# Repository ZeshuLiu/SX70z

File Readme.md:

# SX-70z

## 介绍

### 项目组成
项目中包含几个部分的硬件：

1. [相机主控板](Hardware/MainController)：替换相机机头内原装的控制器，接管相机的控制。
2. [机身控制器](Hardware/Body_controller)：显示当前相机工作状态并提供用于交互的按键。粘贴在机身背部，不会增加相机高度，因此大部分相机包依旧可以通用，与相机主控板连接需要 Fpc 排线。

### 开发

PCB部分除FPC使用嘉立创EDA外均使用KiCad9绘制，仓库提供了相应的工程和光绘(gerber)文件。

机身控制器采用ESP-IDF进行开发

## 性能参数
相机主控可以单独使用，此时可以进行自动测光和曝光，如果需要使用B、T以及手动模式需要配备机身控制器。

**快门速度：** 3s-1/8000s，共 27 档，支持 B 门及 T 门 。 T 门可设置时间，至多5h （非定时T和B门无时间限制）\
**自拍定时：** 0s/2s/5s/10s （倒计时完成后按当前模式自动曝光，倒计时期间挂起其余 Core 1 任务，不受按键干扰）\
**多重曝光：** 最多 11 张（受 MCU 机能限制，曝光过程中无法折叠相机，断电将导致快门保持打开状态造成严重过曝）。多重曝光期间电磁铁持续通电，间隔超过 5 分钟可能导致过热，建议尽快完成所有曝光并吐片。设置方式：长按进入设置菜单，切换 MultiExp 选项（-1 为仅中止/首张防护，0 为正常拍摄，1-10 为额外曝光张数）\
**测光：** 支持 ISO 640 相纸（通过 OPT4001 环境光传感器 + 窗口衰减系数 `METERING_ATTEN_K` 标定），实测与 **Sekonic L-308S** 测光表对比，全快门速度范围（3s – 1/8000s）精度一致，自动测光下最低快门速度 3s  \
**闪光同步：** 插入闪光灯后快门速度自动锁定 1/30s，手动模式可设置慢于 1/30s 进行填充闪光

*SX70的光圈在使用闪光灯时将会根据对焦距离进行收缩，此时调整黑白轮可以控制其光圈大小。本项目依旧保留了该特点，因此在使用闪光灯时请注意对焦距离以及黑白轮的位置*

### 曝光模式 × 闪光灯 行为矩阵

| 模式 | 无闪光灯 | 有闪光灯 |
|------|---------|---------|
| **AUTO** | 测光 → 自动选快门速度 → 普通曝光 | 快门固定 1/30s → 闪光曝光（47ms 预延迟后触发电容引闪） |
| **BULB** | 开快门 → 等 S1T 释放 → 关快门 | SOL2 光圈打开 → 开快门 → 47ms → 闪光 → 等 S1T 释放 |
| **TIME** | 开快门 → 等 S1T 按两次 → 关快门 | SOL2 光圈打开 → 开快门 → 47ms → 闪光 → 等 S1T 按两次 |
| **MANUAL** | 用户指定快门速度 → 普通曝光 | 快门限制在 1/30s，按用户速度计算 gap → 闪光曝光 |

所有模式下，相机任务均运行在 **ESP32 的 Core 1**，按优先级分层隔离，曝光时序不受 WiFi/BLE 干扰。

### 软件架构

```
Core 0:   WiFi 协议栈 + NimBLE BLE + HTTP Server (OTA Web) + 事件回调
Core 1:   相机控制（与射频中断隔离）
  ├─ Shutter  Task  prio 10 — 强时序引脚控制（busy-wait，独占 Core 1）
  ├─ Control  Task  prio 8  — 主控逻辑（按键/模式/S1 快门）
  ├─ Display  Task  prio 5  — SSD1306 I2C 刷屏（200ms 周期）
  └─ Metering Task  prio 3  — OPT4001 测光（1s 周期）
```

模块文件：

| 文件 | 职责 |
|------|------|
| `camera_main.c` | 任务调度、曝光时序、电磁铁/电机控制 |
| `gpio_inputs.c` | GPIO 输入处理：S1/S2 去抖、3D 按键、设置菜单（自拍定时 / 多重曝光 / IP 显示） |
| `display_manager.c` | OLED 帧绘制、倒计时显示、设置菜单布局 |
| `opt4001.c` | OPT4001 环境光传感器 I2C 驱动 |
| `ssd1306.c` | SSD1306 OLED I2C 驱动（esp_lcd 后端，含 `ssd1306_draw_str_black` 反色绘制） |
| `pcf8575.c` | PCF8575 I2C GPIO 扩展驱动 |
| `pin_init.c` | GPIO 引脚初始化 |
| `ota_web.c` | WiFi HTTP OTA 网页升级 |

### 设置菜单

长按 3D 按键的"按下"键进入设置菜单，菜单参数化支持上下键切换选项、短按"按下"键切换调整/浏览模式：

| 选项 | 说明 |
|------|------|
| **SelfTimer** | 自拍定时：0s / 2s / 5s / 10s |
| **MultiExp** | 多重曝光：-1（仅中止，首张防护）/ 0（正常）/ 1-10（额外张数，最多 11 张）|
| **IP Addr** | 只读，显示相机当前 WiFi IP 地址（未连接时显示 "not connected"）|

状态栏右上角同时显示当前自拍定时值与多重曝光剩余张数。

## 样片

## 硬件制造
投产文件集中在 [投产文件](投产文件/)：主控使用 3.5 版 Gerber，机身控制器、机身 FPC 和外壳文件也在其中。BOM、坐标和硬件版本的对应关系仍须按目录说明核对后再下单。PCB 厚度应小于 0.8 mm，主板与机身控制器通过 FPC 连接。完整操作草稿见[复刻与调试指南](Code/SX70z_ESP/SX70_ModelZ/复刻指南.md)。

## 软件

在将机身主控安装至机器内部之前需要将固件通过串口烧录至控制器中。后续可以通过 OTA 无线升级，无需拆机。

**首次 WiFi 配网：**

首次开机相机没有 WiFi 凭据，会通过 BLE 广播 `SX70z_POP`。手机下载 **ESP BLE Provisioning** 应用（iOS/Android 应用商店均有），打开后选择配网，输入配对密钥 `sx70z123`，选择家中 WiFi 并输入密码即可。配网成功后凭据会存入 NVS，下次开机自动连接。

**OTA 升级方式：**
1. 相机开机连接 WiFi（通过 BLE 配网或已保存的凭据自动连接）
2. 手机或电脑连接同一局域网，浏览器打开相机 IP（OLED 设置菜单中可查看）
3. 选择编译好的 `.bin` 固件文件上传
4. 上传完成自动重启，新固件生效（Bootloader 会校验固件有效性，异常自动回滚）

快门可通过 `http://<相机IP>/calibration` 页面校准并保存，无需修改源码。先将 1/8000 调到快门形成一个小缝，其余档位可参考该档的偏移量在默认值基础上调整，再逐档测量确认；具体操作可搜索“陆工主板 快门校准”教程，也可使用[快门速度测试器](https://github.com/ZeshuLiu/ShutterSpeedCalibrator)。详细说明见[复刻与调试指南](Code/SX70z_ESP/SX70_ModelZ/复刻指南.md)。

## 组装
> 提示：组装需要一些基本的工具：电烙铁、撬棒和镊子。 \
大多数sx70相机的螺丝都是非常特殊的1mm x 1mm 宝丽来螺丝，拆卸需要特殊的螺丝刀，可以从咸鱼买一把或者自己磨一个。 \
在操作之前推荐先浏览以下内容[Disassembly Guide](https://instantphotography.files.wordpress.com/2010/12/polaroid-sx-70-camera-repair-book.pdf) 或者 [SX70 camera 125ASA to 600ASA conversion](https://opensx70.com/tutorials/100-600-conversion/).

拆卸后对原本主板进行替换即可，如需要机身控制器则将左上角焊盘焊线引出即可通过转接板连接机身控制器。焊接FPC时建议使用含铅(低温)焊锡，否则有损伤机器FPC的风险。只需要将原本的拆掉并且替换上去即可，对于有焊接及机身拆装经验的人来说难度不高。

### 相关开源软件

1. 项目受到了[OPSX ](https://github.com/sunyitong/OPSX)和[openSX70](https://github.com/openSX70)的启发。

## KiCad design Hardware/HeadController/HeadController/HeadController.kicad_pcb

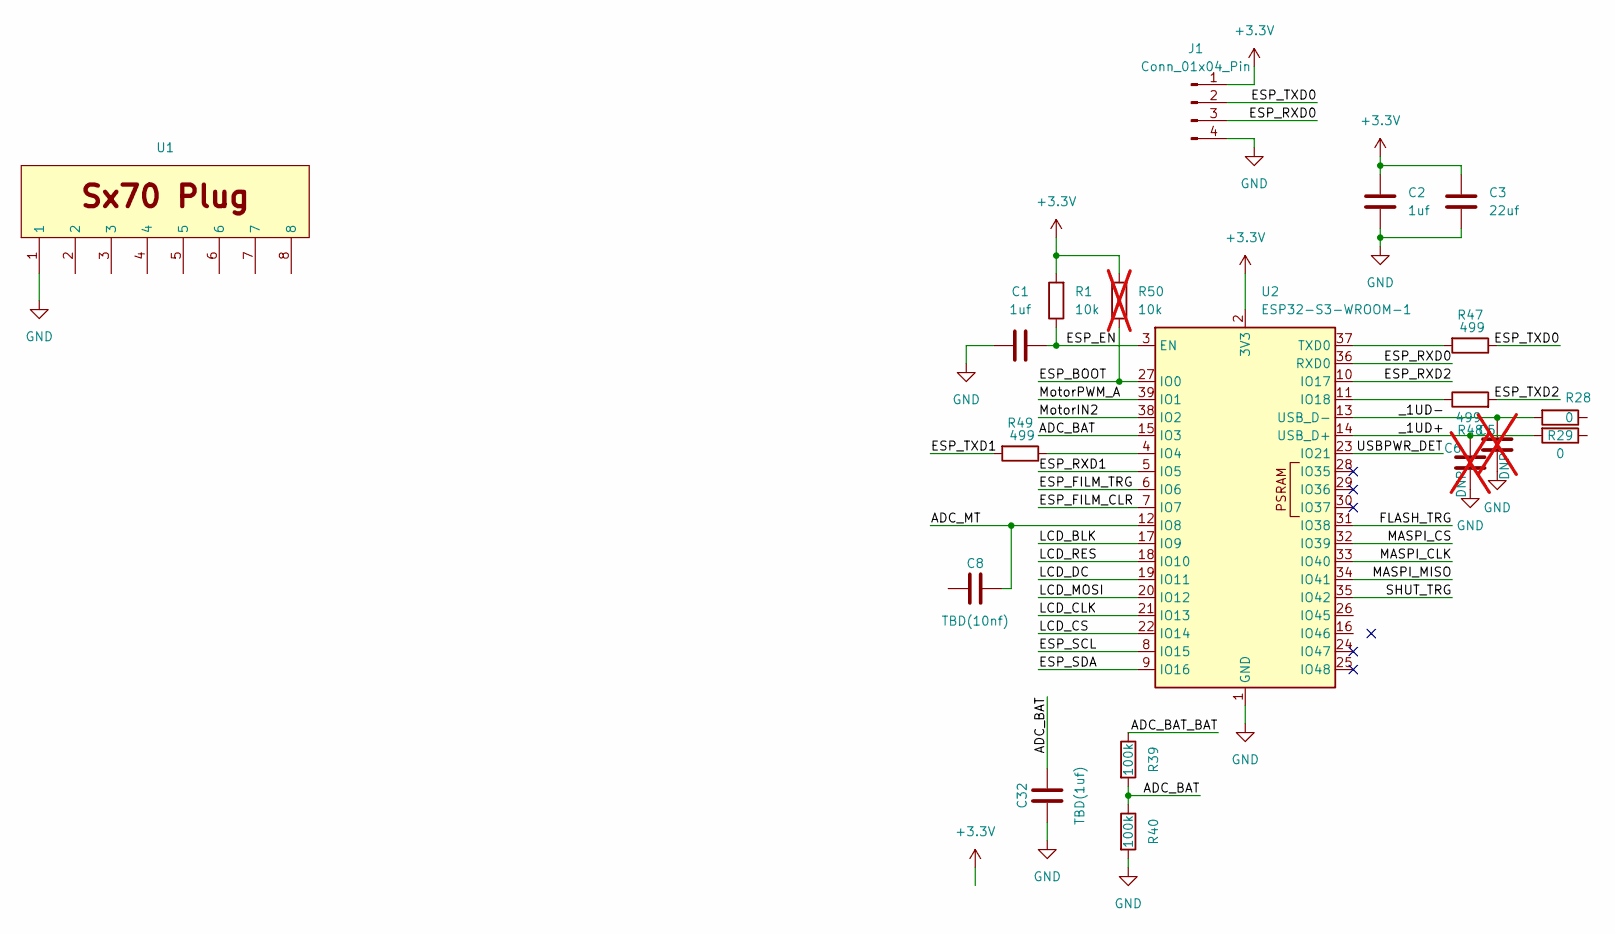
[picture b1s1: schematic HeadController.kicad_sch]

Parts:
C1, C2: 1uf; C_0603_1608Metric
C3: 22uf; C_0805_2012Metric
C5, C6: DNP; C_0603_1608Metric; not fitted
C8: TBD(10nf); C_0603_1608Metric
C32: TBD(1uf); C_0603_1608Metric
J1: Conn_01x04_Pin; PinHeader_1x04_P1.27mm_Vertical
R1: 10k; R_0603_1608Metric
R28, R29: 0; R_0603_1608Metric
R39, R40: 100k; R_0603_1608Metric
R47, R48, R49: 499; R_0603_1608Metric
R50: 10k; R_0603_1608Metric; not fitted
U1: SX70_Flash_Plug
U2: ESP32-S3-WROOM-1

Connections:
+3.3V: C2.2, C3.2, J1.1, R1.2, R50.2, U2.2 (3V3)
/ADC_BAT: C32.2, R39.2, R40.1, U2.15 (IO3)
/ADC_BAT_BAT: R39.1
/ADC_MT: C8.2, U2.12 (IO8)
/ESP_BOOT: R50.1, U2.27 (IO0)
/ESP_EN: C1.2, R1.1, U2.3 (EN)
/ESP_FILM_CLR: U2.7 (IO7)
/ESP_FILM_TRG: U2.6 (IO6)
/ESP_RXD0: J1.3, U2.36 (RXD0)
/ESP_RXD1: U2.5 (IO5)
/ESP_RXD2: U2.10 (IO17)
/ESP_SCL: U2.8 (IO15)
/ESP_SDA: U2.9 (IO16)
/ESP_TXD0: J1.2, R47.1
/ESP_TXD1: R49.2
/ESP_TXD2: R48.2
/FLASH_TRG: U2.31 (IO38)
/LCD_BLK: U2.17 (IO9)
/LCD_CLK: U2.21 (IO13)
/LCD_CS: U2.22 (IO14)
/LCD_DC: U2.19 (IO11)
/LCD_MOSI: U2.20 (IO12)
/LCD_RES: U2.18 (IO10)
/MASPI_CLK: U2.33 (IO40)
/MASPI_CS: U2.32 (IO39)
/MASPI_MISO: U2.34 (IO41)
/MotorIN2: U2.38 (IO2)
/MotorPWM_A: U2.39 (IO1)
/SHUT_TRG: U2.35 (IO42)
/USBPWR_DET: U2.23 (IO21)
/_1UD+: C6.2, R29.2, U2.14 (USB_D+)
/_1UD-: C5.2, R28.2, U2.13 (USB_D-)
GND: C1.1, C2.1, C3.1, C5.1, C6.1, C32.1, J1.4, R40.2, U1.1 (1_1), U2.1 (GND), U2.40 (GND), U2.41 (GND)
unnamed: R49.1, U2.4 (IO4)
unnamed: R48.1, U2.11 (IO18)
unnamed: R47.2, U2.37 (TXD0)

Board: 2 copper layers, 19 parts (0 on the bottom side), 13 nets, no tracks yet.

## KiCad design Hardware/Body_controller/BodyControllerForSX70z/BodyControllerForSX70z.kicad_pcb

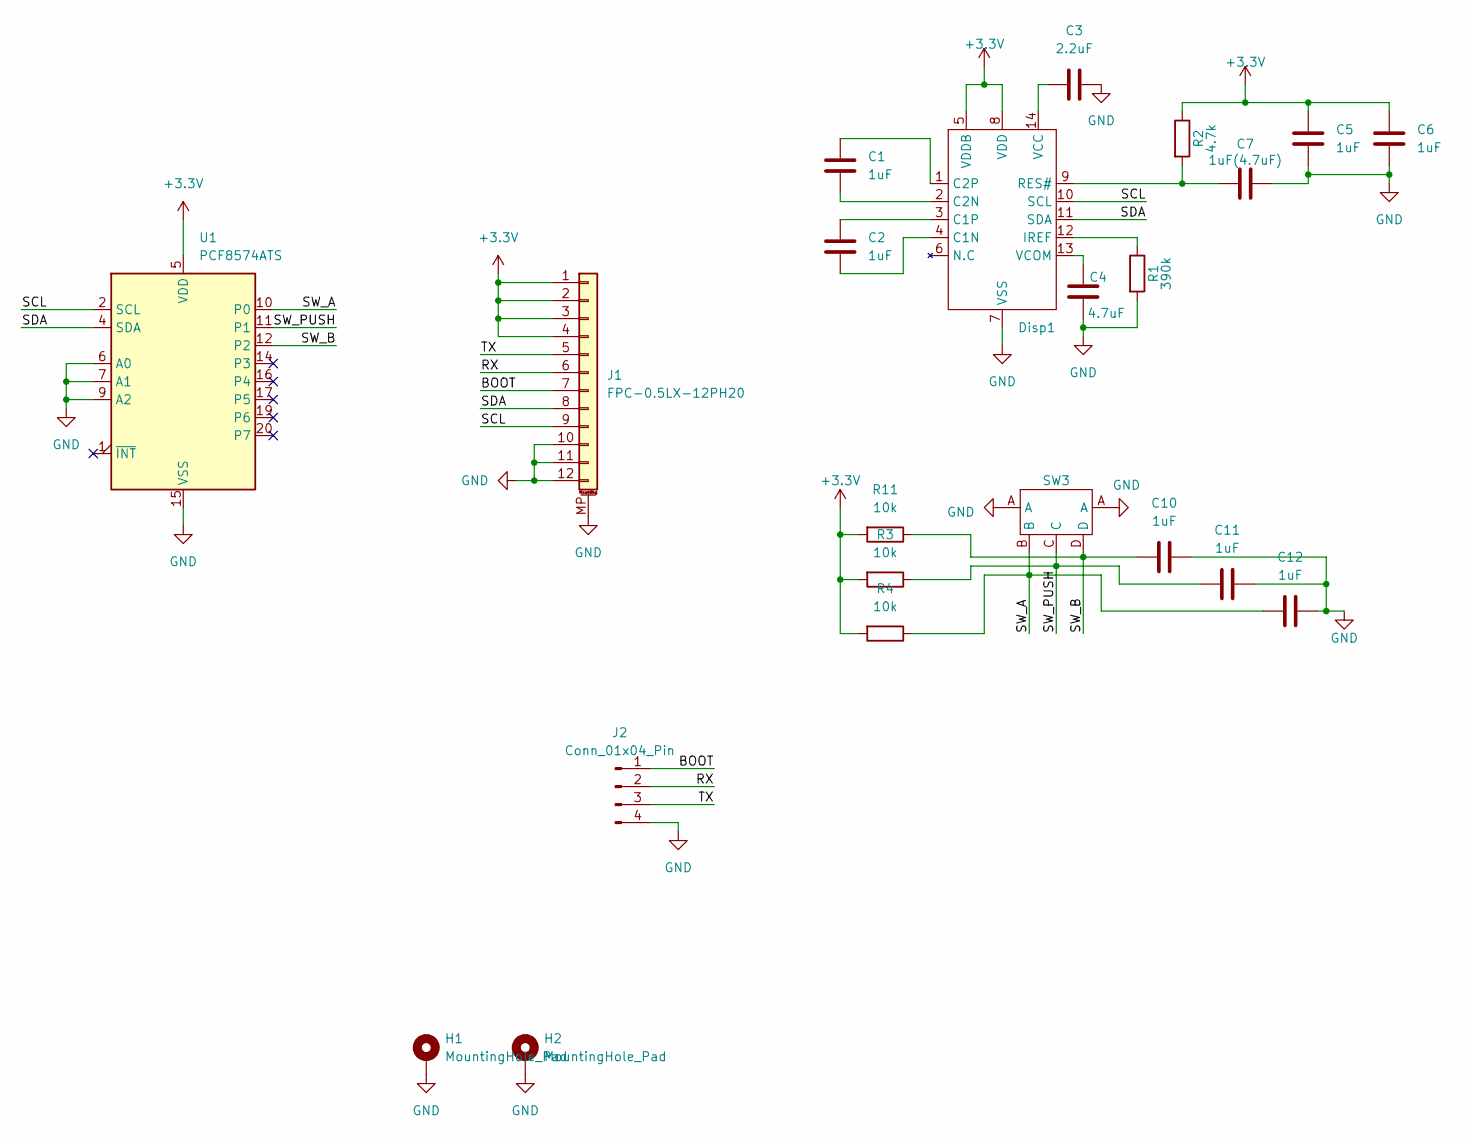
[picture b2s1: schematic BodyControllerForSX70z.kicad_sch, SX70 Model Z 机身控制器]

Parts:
C1, C2, C5, C6, C10, C11, C12: 1uF; C_0603_1608Metric_Pad1.08x0.95mm_HandSolder
C3: 2.2uF; C_0603_1608Metric_Pad1.08x0.95mm_HandSolder
C4: 4.7uF; C_0603_1608Metric_Pad1.08x0.95mm_HandSolder
C7: 1uF(4.7uF); C_0603_1608Metric_Pad1.08x0.95mm_HandSolder
Disp1: SSD1306_0.91_i2c
H1, H2: MountingHole_Pad; MountingHole_3.2mm_M3_DIN965_Pad
J1: FPC-0.5LX-12PH20
J2: Conn_01x04_Pin; PinHeader_1x04_P2.54mm_Horizontal
R1: 390k; R_0603_1608Metric_Pad0.98x0.95mm_HandSolder
R2: 4.7k; R_0603_1608Metric_Pad0.98x0.95mm_HandSolder
R3, R4, R11: 10k; R_0603_1608Metric_Pad0.98x0.95mm_HandSolder
SW3: Direction3 Pin5
U1: PCF8574ATS; SSOP-20_4.4x6.5mm_P0.65mm

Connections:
+3.3V: C5.1, C6.1, Disp1.5 (VDDB), Disp1.8 (VDD), J1.1, J1.2, J1.3, J1.4, R2.1, R3.2, R4.2, R11.2, U1.5 (VDD)
/BOOT: J1.7, J2.1
/RX: J1.6, J2.2
/SCL: Disp1.10 (SCL), J1.9, U1.2 (SCL)
/SDA: Disp1.11 (SDA), J1.8, U1.4 (SDA)
/SW_A: C12.1, R4.1, SW3.B, U1.10 (P0)
/SW_B: C10.1, R11.1, SW3.D, U1.12 (P2)
/SW_PUSH: C11.1, R3.1, SW3.C, U1.11 (P1)
/TX: J1.5, J2.3
GND: C3.2, C4.1, C5.2, C6.2, C7.2, C10.2, C11.2, C12.2, Disp1.7 (VSS), H1.1, H2.1, J1.10, J1.11, J1.12, J1.MP (MountPin), J2.4, R1.2, SW3.A, U1.6 (A0), U1.7 (A1), U1.9 (A2), U1.15 (VSS)
unnamed: C2.2, Disp1.4 (C1N)
unnamed: C2.1, Disp1.3 (C1P)
unnamed: C1.2, Disp1.2 (C2N)
unnamed: C1.1, Disp1.1 (C2P)
unnamed: Disp1.12 (IREF), R1.1
unnamed: C7.1, Disp1.9 (RES#), R2.2
unnamed: C3.1, Disp1.14 (VCC)
unnamed: C4.2, Disp1.13 (VCOM)

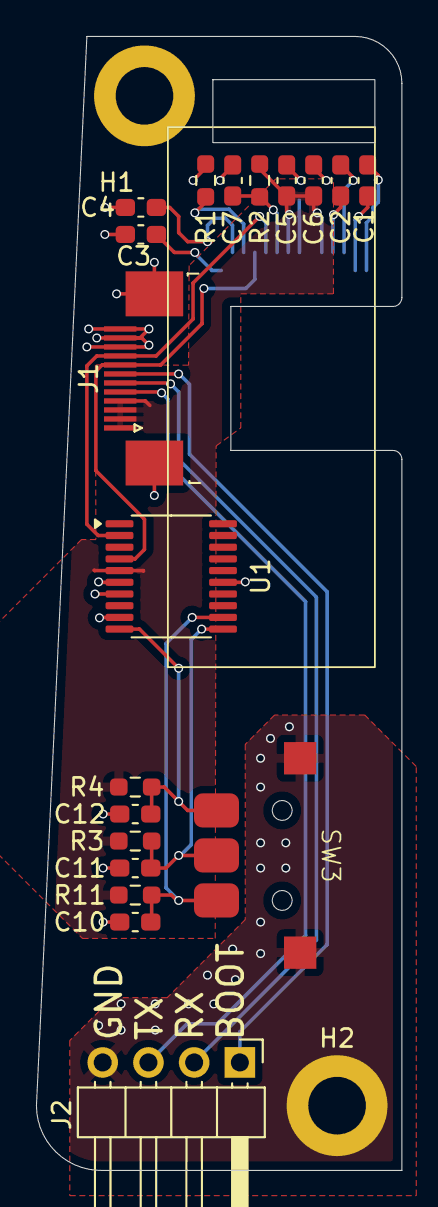
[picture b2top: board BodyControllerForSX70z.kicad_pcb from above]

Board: 2 copper layers, 20.3 x 63.0 mm, 22 parts (1 on the bottom side), 18 nets.

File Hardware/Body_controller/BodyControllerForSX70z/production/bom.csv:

Designator,Footprint,Quantity,Value,LCSC Part #
"C1, C10, C11, C12, C2, C5, C6",0603,7,1uF,
C3,0603,1,2.2uF,
C4,0603,1,4.7uF,
C7,0603,1,1uF(4.7uF),
DISP1,SSD1306_0.91_i2c,1,~,
J1,FPC-0.5LX-12PH20,1,FPC-0.5LX-12PH20,
J2,PinHeader_1x04_P2.54mm_Horizontal,1,Conn_01x04_Pin,
R1,0603,1,390k,
"R11, R3, R4",0603,3,10k,
R2,0603,1,4.7k,
SW3,Direction3 Pin5,1,~,
U1,SSOP-20_4.4x6.5mm_P0.65mm,1,PCF8574ATS,

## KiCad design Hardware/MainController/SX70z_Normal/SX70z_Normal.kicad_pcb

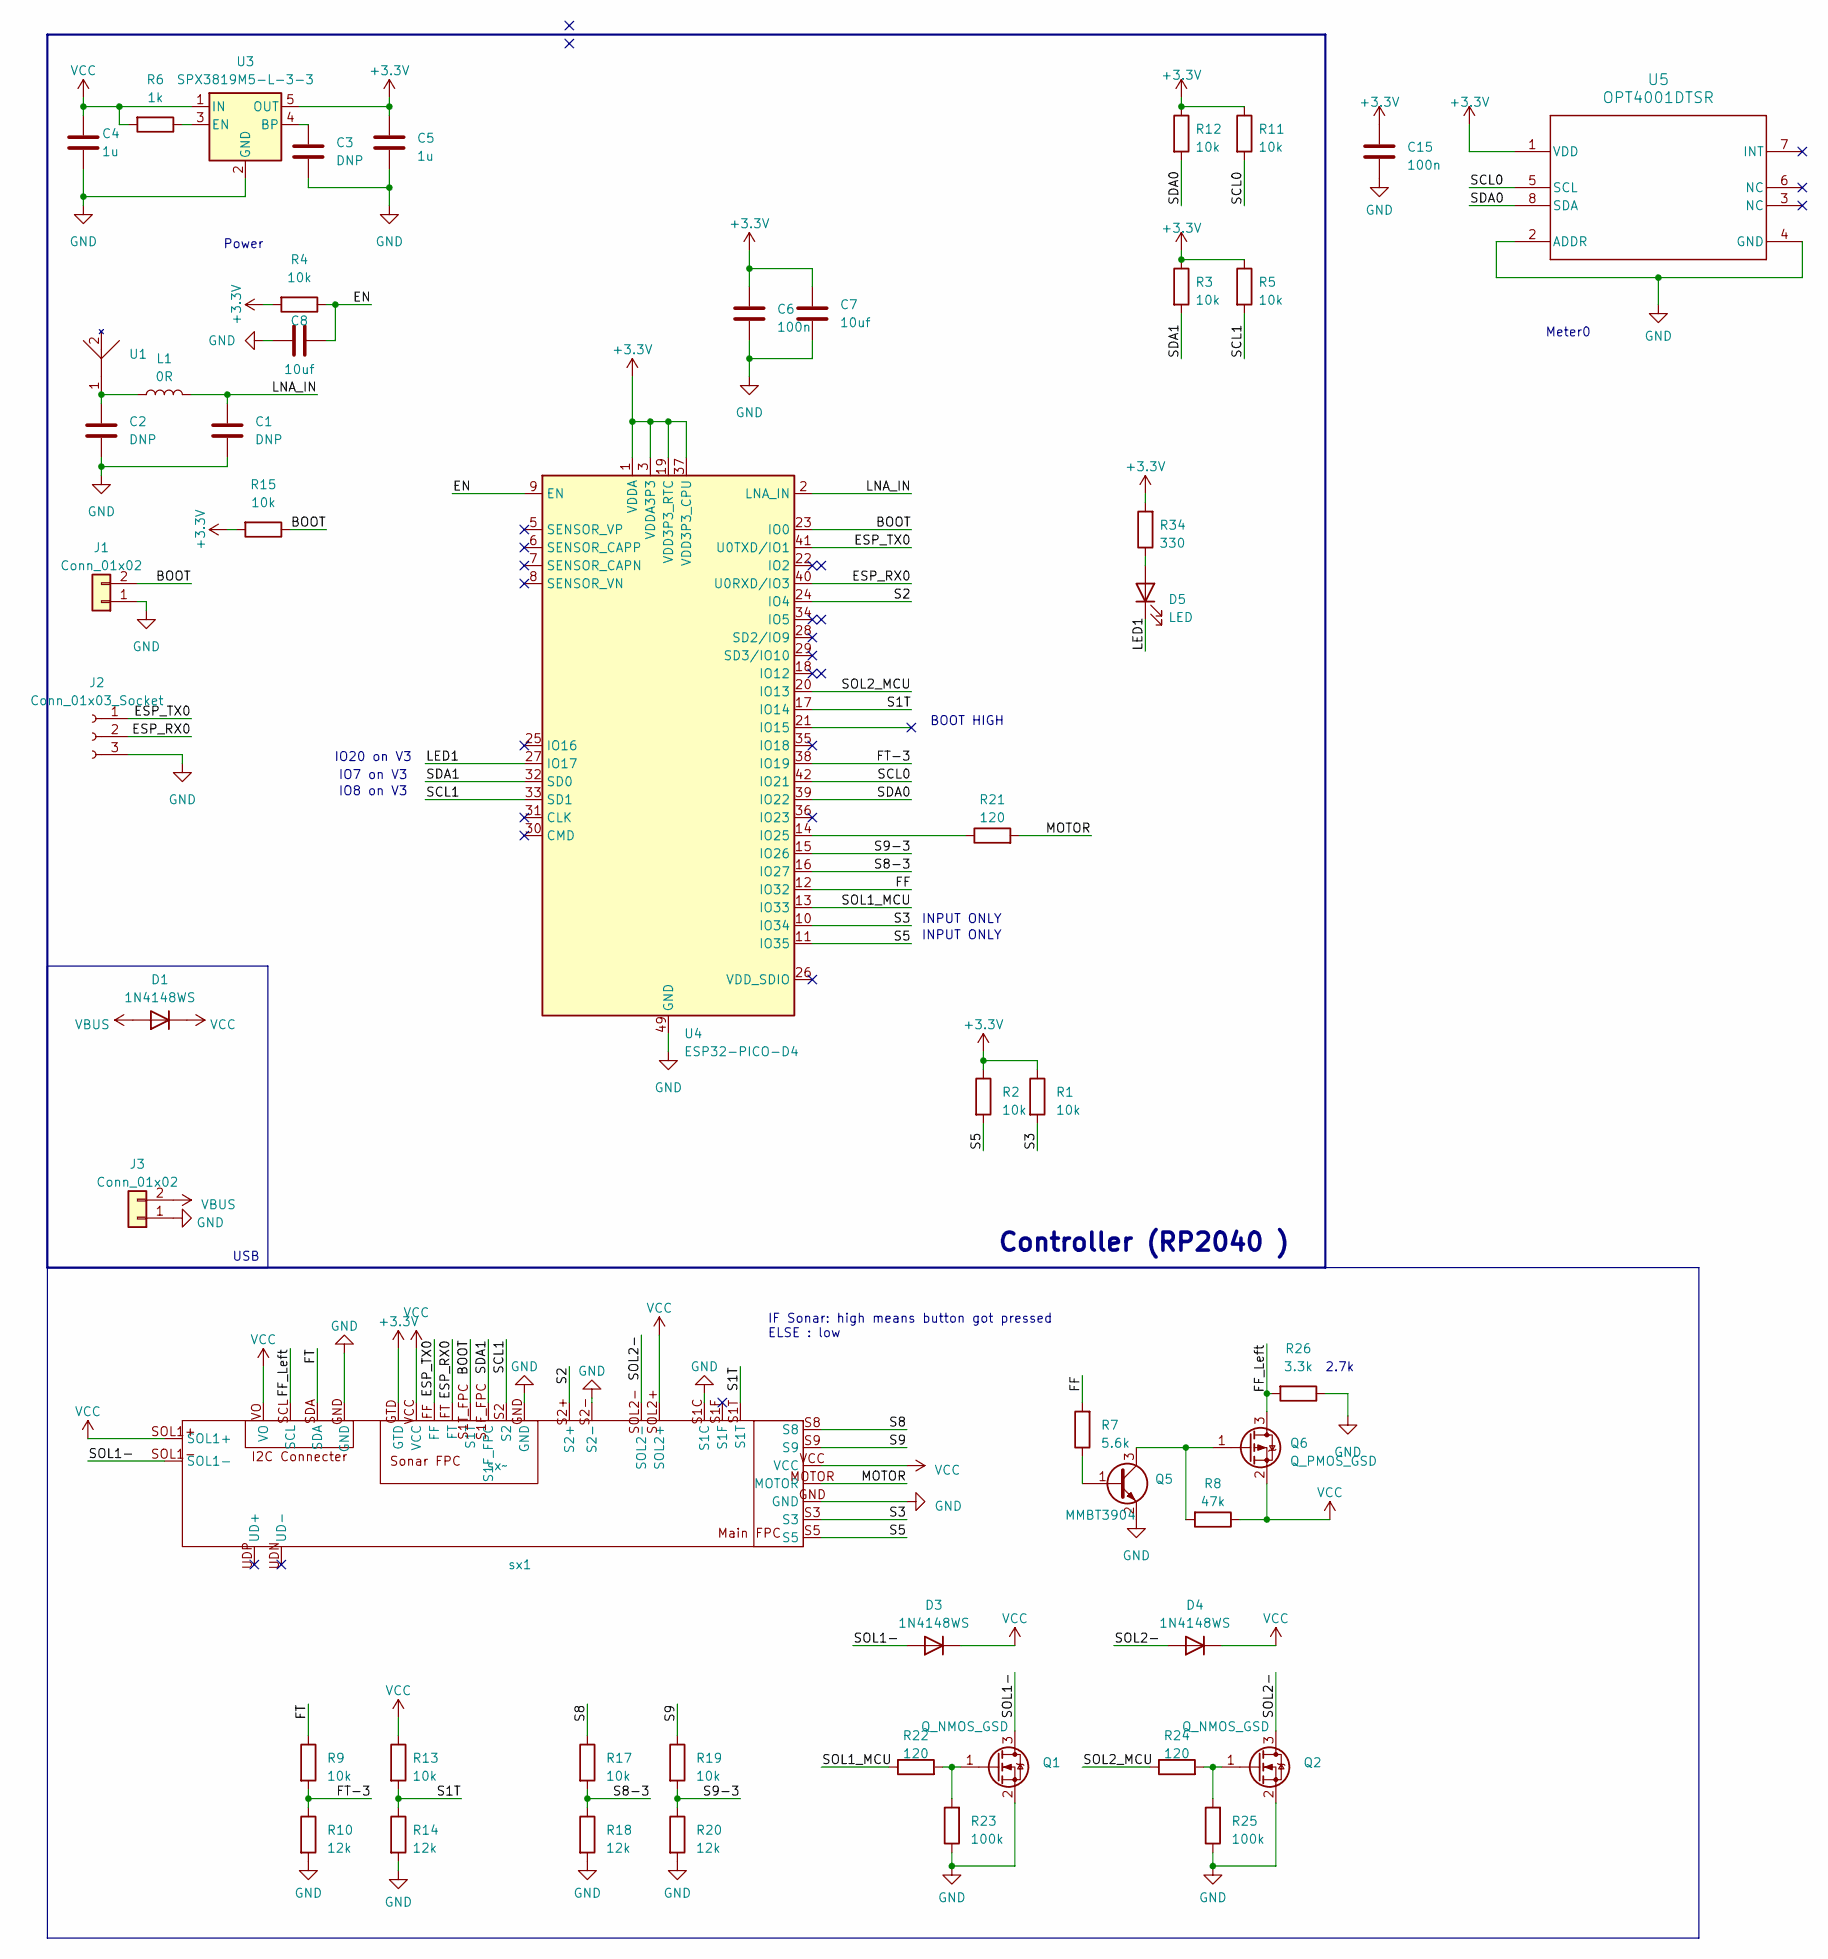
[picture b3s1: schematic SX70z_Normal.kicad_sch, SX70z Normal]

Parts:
C1, C2: DNP; C_0402_1005Metric
C3: DNP; C_0402_1005Metric_Pad0.74x0.62mm_HandSolder
C4, C5: 1u; C_0402_1005Metric_Pad0.74x0.62mm_HandSolder
C6, C15: 100n; C_0402_1005Metric_Pad0.74x0.62mm_HandSolder
C7: 10uf; C_0402_1005Metric_Pad0.74x0.62mm_HandSolder
C8: 10uf; C_0402_1005Metric
D1, D3, D4: 1N4148WS; D_SOD-323
D5: LED; D_0603_1608Metric_Pad1.05x0.95mm_HandSolder
J1, J3: Conn_01x02; PinHeader_1x02_P2.54mm_Vertical
J2: Conn_01x03_Socket; PinHeader_1x03_P2.54mm_Vertical
L1: 0R; L_0402_1005Metric
Q1, Q2: Q_NMOS_GSD; SOT-23
Q5: MMBT3904; SOT-23
Q6: Q_PMOS_GSD; SOT-23
R1, R2, R3, R4, R5, R9, R11, R12, R13, R15, R17, R19: 10k; R_0402_1005Metric_Pad0.72x0.64mm_HandSolder
R6: 1k; R_0402_1005Metric_Pad0.72x0.64mm_HandSolder
R7: 5.6k; R_0402_1005Metric_Pad0.72x0.64mm_HandSolder
R8: 47k; R_0402_1005Metric_Pad0.72x0.64mm_HandSolder
R10, R14, R18, R20: 12k; R_0402_1005Metric_Pad0.72x0.64mm_HandSolder
R21, R22, R24: 120; R_0402_1005Metric_Pad0.72x0.64mm_HandSolder
R23, R25: 100k; R_0402_1005Metric_Pad0.72x0.64mm_HandSolder
R26: 3.3k; R_0402_1005Metric_Pad0.72x0.64mm_HandSolder
R34: 330; R_0402_1005Metric_Pad0.72x0.64mm_HandSolder
U1: AN2051-245
U3: SPX3819M5-L-3-3; SOT-23-5
U4: ESP32-PICO-D4; QFN-48-1EP_7x7mm_P0.5mm_EP5.1x5.1mm_ThermalVias
U5: OPT4001DTSR; OPT4001-DTS0008A-MFG
sx1: sx~; sx70_i2c

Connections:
+3.3V: C5.1, C6.1, C7.1, C15.1, R1.1, R2.1, R3.1, R4.2, R5.1, R11.1, R12.1, R15.2, R34.2, U3.5 (OUT), U4.1 (VDDA), U4.3 (VDDA3P3), U4.4 (VDDA3P3), U4.19 (VDD3P3_RTC), U4.37 (VDD3P3_CPU), U4.43 (VDDA), U4.46 (VDDA), U5.1 (VDD), sx1.GTD
/BOOT: J1.2, R15.1, U4.23 (IO0), sx1.S1T_FPC (S1T)
/EN: C8.2, R4.1, U4.9 (EN)
/ESP_RX0: J2.2, U4.40 (U0RXD/IO3), sx1.FT
/ESP_TX0: J2.1, U4.41 (U0TXD/IO1), sx1.FF
/FF: R7.2, U4.12 (IO32)
/FF_Left: Q6.3 (D), R26.2, sx1.SCL
/FT: R9.1, sx1.SDA
/FT-3: R9.2, R10.1, U4.38 (IO19)
/LED1: D5.1 (K), U4.27 (IO17)
/LNA_IN: C1.1, L1.2, U4.2 (LNA_IN)
/MOTOR: R21.2, sx1.MOTOR
/S1T: R13.2, R14.1, U4.17 (IO14), sx1.S1T
/S2: U4.24 (IO4), sx1.S2+
/S3: R1.2, U4.10 (IO34), sx1.S3
/S5: R2.2, U4.11 (IO35), sx1.S5
/S8: R17.1, sx1.S8
/S8-3: R17.2, R18.1, U4.16 (IO27)
/S9: R19.1, sx1.S9
/S9-3: R19.2, R20.1, U4.15 (IO26)
/SCL0: R11.2, U4.42 (IO21), U5.5 (SCL)
/SCL1: R5.2, U4.33 (SD1), sx1.S2
/SDA0: R12.2, U4.39 (IO22), U5.8 (SDA)
/SDA1: R3.2, U4.32 (SD0), sx1.S1F_FPC
/SOL1-: D3.2 (A), Q1.3 (D), sx1.SOL1-
/SOL1_MCU: R22.1, U4.13 (IO33)
/SOL2-: D4.2 (A), Q2.3 (D), sx1.SOL2-
/SOL2_MCU: R24.1, U4.20 (IO13)
GND: C1.2, C2.2, C3.2, C4.2, C5.2, C6.2, C7.2, C8.1, C15.2, J1.1, J2.3, J3.1, Q1.2 (S), Q2.2 (S), Q5.2 (E), R10.2, R14.2, R18.2, R20.2, R23.1, R25.1, R26.1, U3.2 (GND), U4.49 (GND), U5.2 (ADDR), U5.4 (GND), sx1.GND, sx1.S1C, sx1.S2-
unnamed: C2.1, L1.1, U1.1
unnamed: D5.2 (A), R34.1
unnamed: Q1.1 (G), R22.2, R23.2
unnamed: Q2.1 (G), R24.2, R25.2
unnamed: Q5.1 (B), R7.1
unnamed: Q5.3 (C), Q6.1 (G), R8.2
unnamed: C3.1, U3.4 (BP)
unnamed: R6.1, U3.3 (EN)
unnamed: R21.1, U4.14 (IO25)
VBUS: D1.2 (A), J3.2
VCC: C4.1, D1.1 (K), D3.1 (K), D4.1 (K), Q6.2 (S), R6.2, R8.1, R13.1, U3.1 (IN), sx1.SOL1+, sx1.SOL2+, sx1.VCC, sx1.VO

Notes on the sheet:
Meter0
Power
2.7k
IF Sonar: high means button got pressed ELSE : low
Controller (RP2040 )
IO8 on V3
IO7 on V3
INPUT ONLY
BOOT HIGH
IO20 on V3
USB

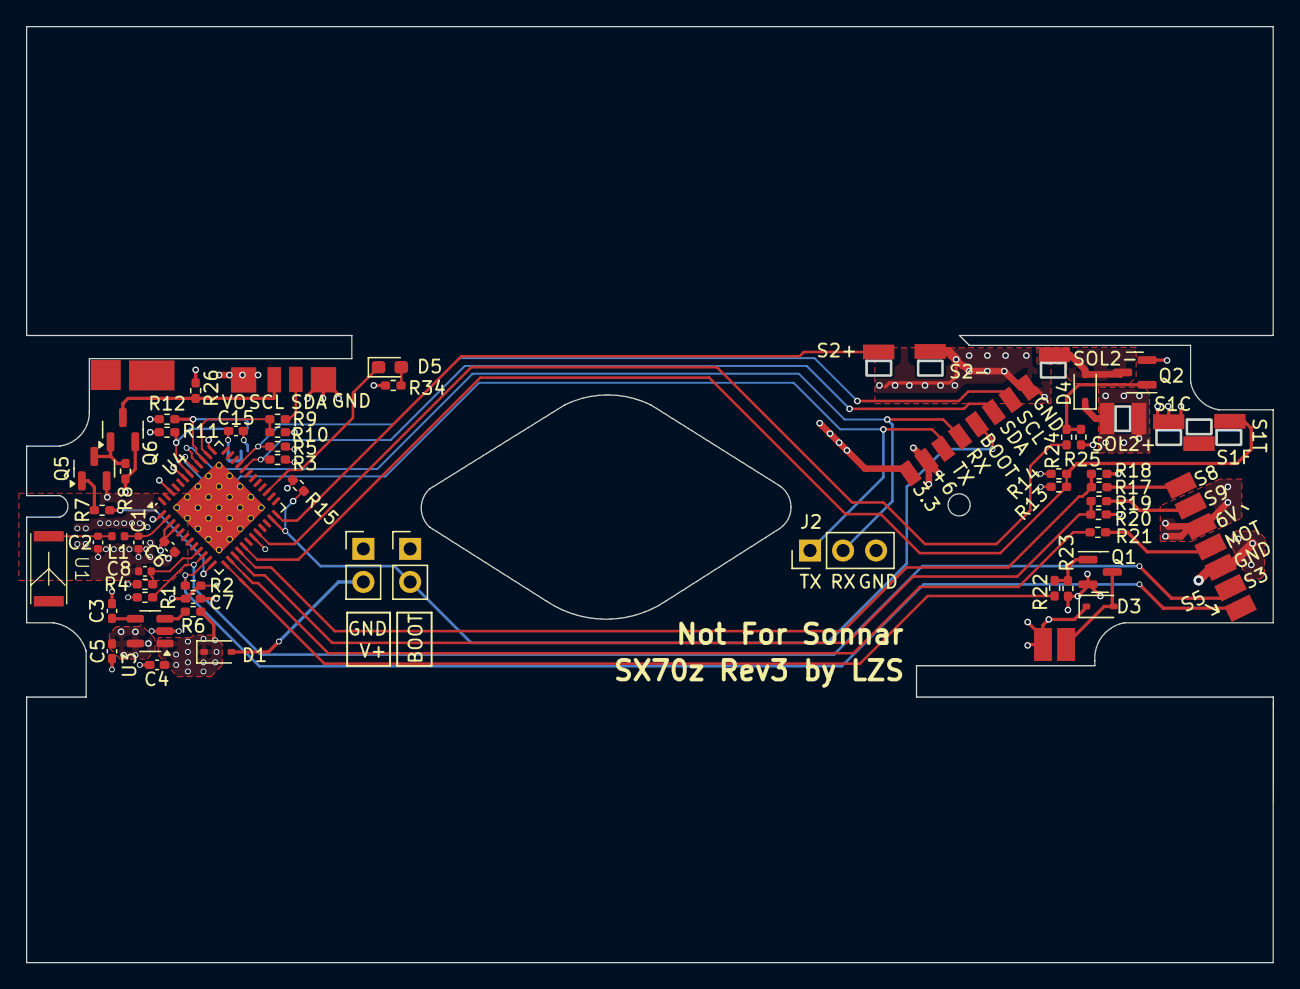
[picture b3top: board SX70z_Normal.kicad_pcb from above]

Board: 4 copper layers, 95.9 x 72.0 mm, 52 parts (1 on the bottom side), 40 nets.

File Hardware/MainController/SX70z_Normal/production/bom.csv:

Designator,Footprint,Quantity,Value,LCSC Part #
"C1, C2, C3",402,3,DNP,
"C15, C6",402,2,100n,
"C4, C5",402,2,1u,
C7,402,1,10uf,
"D1, D3, D4",D_SOD-323,3,1N4148WS,
D5,603,1,LED,
"J1, J3",PinHeader_1x02_P2.54mm_Vertical,2,Conn_01x02,
J2,PinHeader_1x03_P2.54mm_Vertical,1,Conn_01x03_Socket,
L1,402,1,0R,
"Q1, Q2",SOT-23,2,Q_NMOS_GSD,
Q5,SOT-23,1,MMBT3904,
Q6,SOT-23,1,Q_PMOS_GSD,
"R1, R4, R11, R12, R13, R17, R19, R2, R3, R5, R9",402,10,10k,
"R10, R14, R18, R20",402,4,12k,
"R21, R22, R24",402,3,120,
"R23, R25",402,2,100k,
R26,402,1,2.7k,
R34,402,2,330,
R6,402,1,1k,
R7,402,1,5.6k,
R8,402,1,47k,
SX1,sx70_i2c,1,sx~,
U1,AN2051-245,1,~,
U3,SOT-23-5,1,SPX3819M5-L-3-3,
U4,QFN-48-1EP_7x7mm_P0.5mm_EP5.1x5.1mm_ThermalVias,1,ESP32-PICO-D4,
U5,OPT4001-DTS0008A-MFG,1,OPT4001DTSR,

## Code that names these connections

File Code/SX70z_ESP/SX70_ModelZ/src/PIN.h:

#pragma once

// I2c部分引脚定义
#define SCL0_PIN GPIO_NUM_21
#define SDA0_PIN GPIO_NUM_22

#define SCL1_PIN GPIO_NUM_8
#define SDA1_PIN GPIO_NUM_7

// #define SCL1_PIN GPIO_NUM_12 // 这个只用于开发板测试， 实际需要用上面注释掉的引脚 7 和 8
// #define SDA1_PIN GPIO_NUM_13 // 这个只用于开发板测试， 实际需要用上面注释掉的引脚 7 和 8

// 外设（输出）引脚定义
#define LED1_PIN GPIO_NUM_20 // 板载LED灯 低电平点亮

#define LED_TEST_PIN GPIO_NUM_2 // 开发板LED灯，实际系统里面没有 低电平点亮

// 相机机身（输入）引脚定义
#define S1T_PIN GPIO_NUM_14 // 机身快门按钮 低电平有效，外部拉高

#define S2_PIN GPIO_NUM_4   // 闪光灯检测引脚 低电平表示有闪光灯，初始化时需要芯片拉高
#define S3_PIN GPIO_NUM_34  // 机身反光板位置监测1 有外部拉高
#define S5_PIN GPIO_NUM_35  // 机身反光板位置监测2 有外部拉高

// 相机机身（输出）引脚定义
#define SOL1_PIN GPIO_NUM_33    // 快门动作 高电平动作，初始化为低
#define SOL2_PIN GPIO_NUM_13    // 光圈动作 高电平动作，初始化为低
#define MOTOR_PIN GPIO_NUM_25   // 机身动作 高电平动作，初始化为低
#define FF_PIN GPIO_NUM_32      // 闪光灯闪光 高电平动作，初始化为低

// PCF8575 3D 按键引脚（位偏移，对应 RP2040 pins.h）
#define PCF_BUTTON3D_DOWN   10  // 下键
#define PCF_BUTTON3D_UP     8   // 上键
#define PCF_BUTTON3D_PUSH   9   // 按下键

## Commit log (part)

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2026-06-03 refactor: 闪光灯检测与拍摄模式分离
    - camera_state_t 新增 has_flash 字段，control_task 统一维护
    - update_mode_display() 同步设 shut_mode（menu 变化时自动映射）
    - 删除 control_task 中 flash_debounce 覆写 shut_mode 的耦合
    - AUTO 闪光灯同步改用 has_flash
    - display_manager.c 改用 state->has_flash，移除 PIN.h/gpio.h
    - shutter_task 曝光阶段合并普通/闪光子路径，共用第5步关快门
2026-06-03 拆分GPIO相关代码，未测试
2026-06-03 Change image zoom level in Readme.md
    Updated image zoom style in the introduction section.
2026-06-06 更新了UI，T门B门菜单合并，T模式支持定时曝光
2026-06-07 更改Readmen
